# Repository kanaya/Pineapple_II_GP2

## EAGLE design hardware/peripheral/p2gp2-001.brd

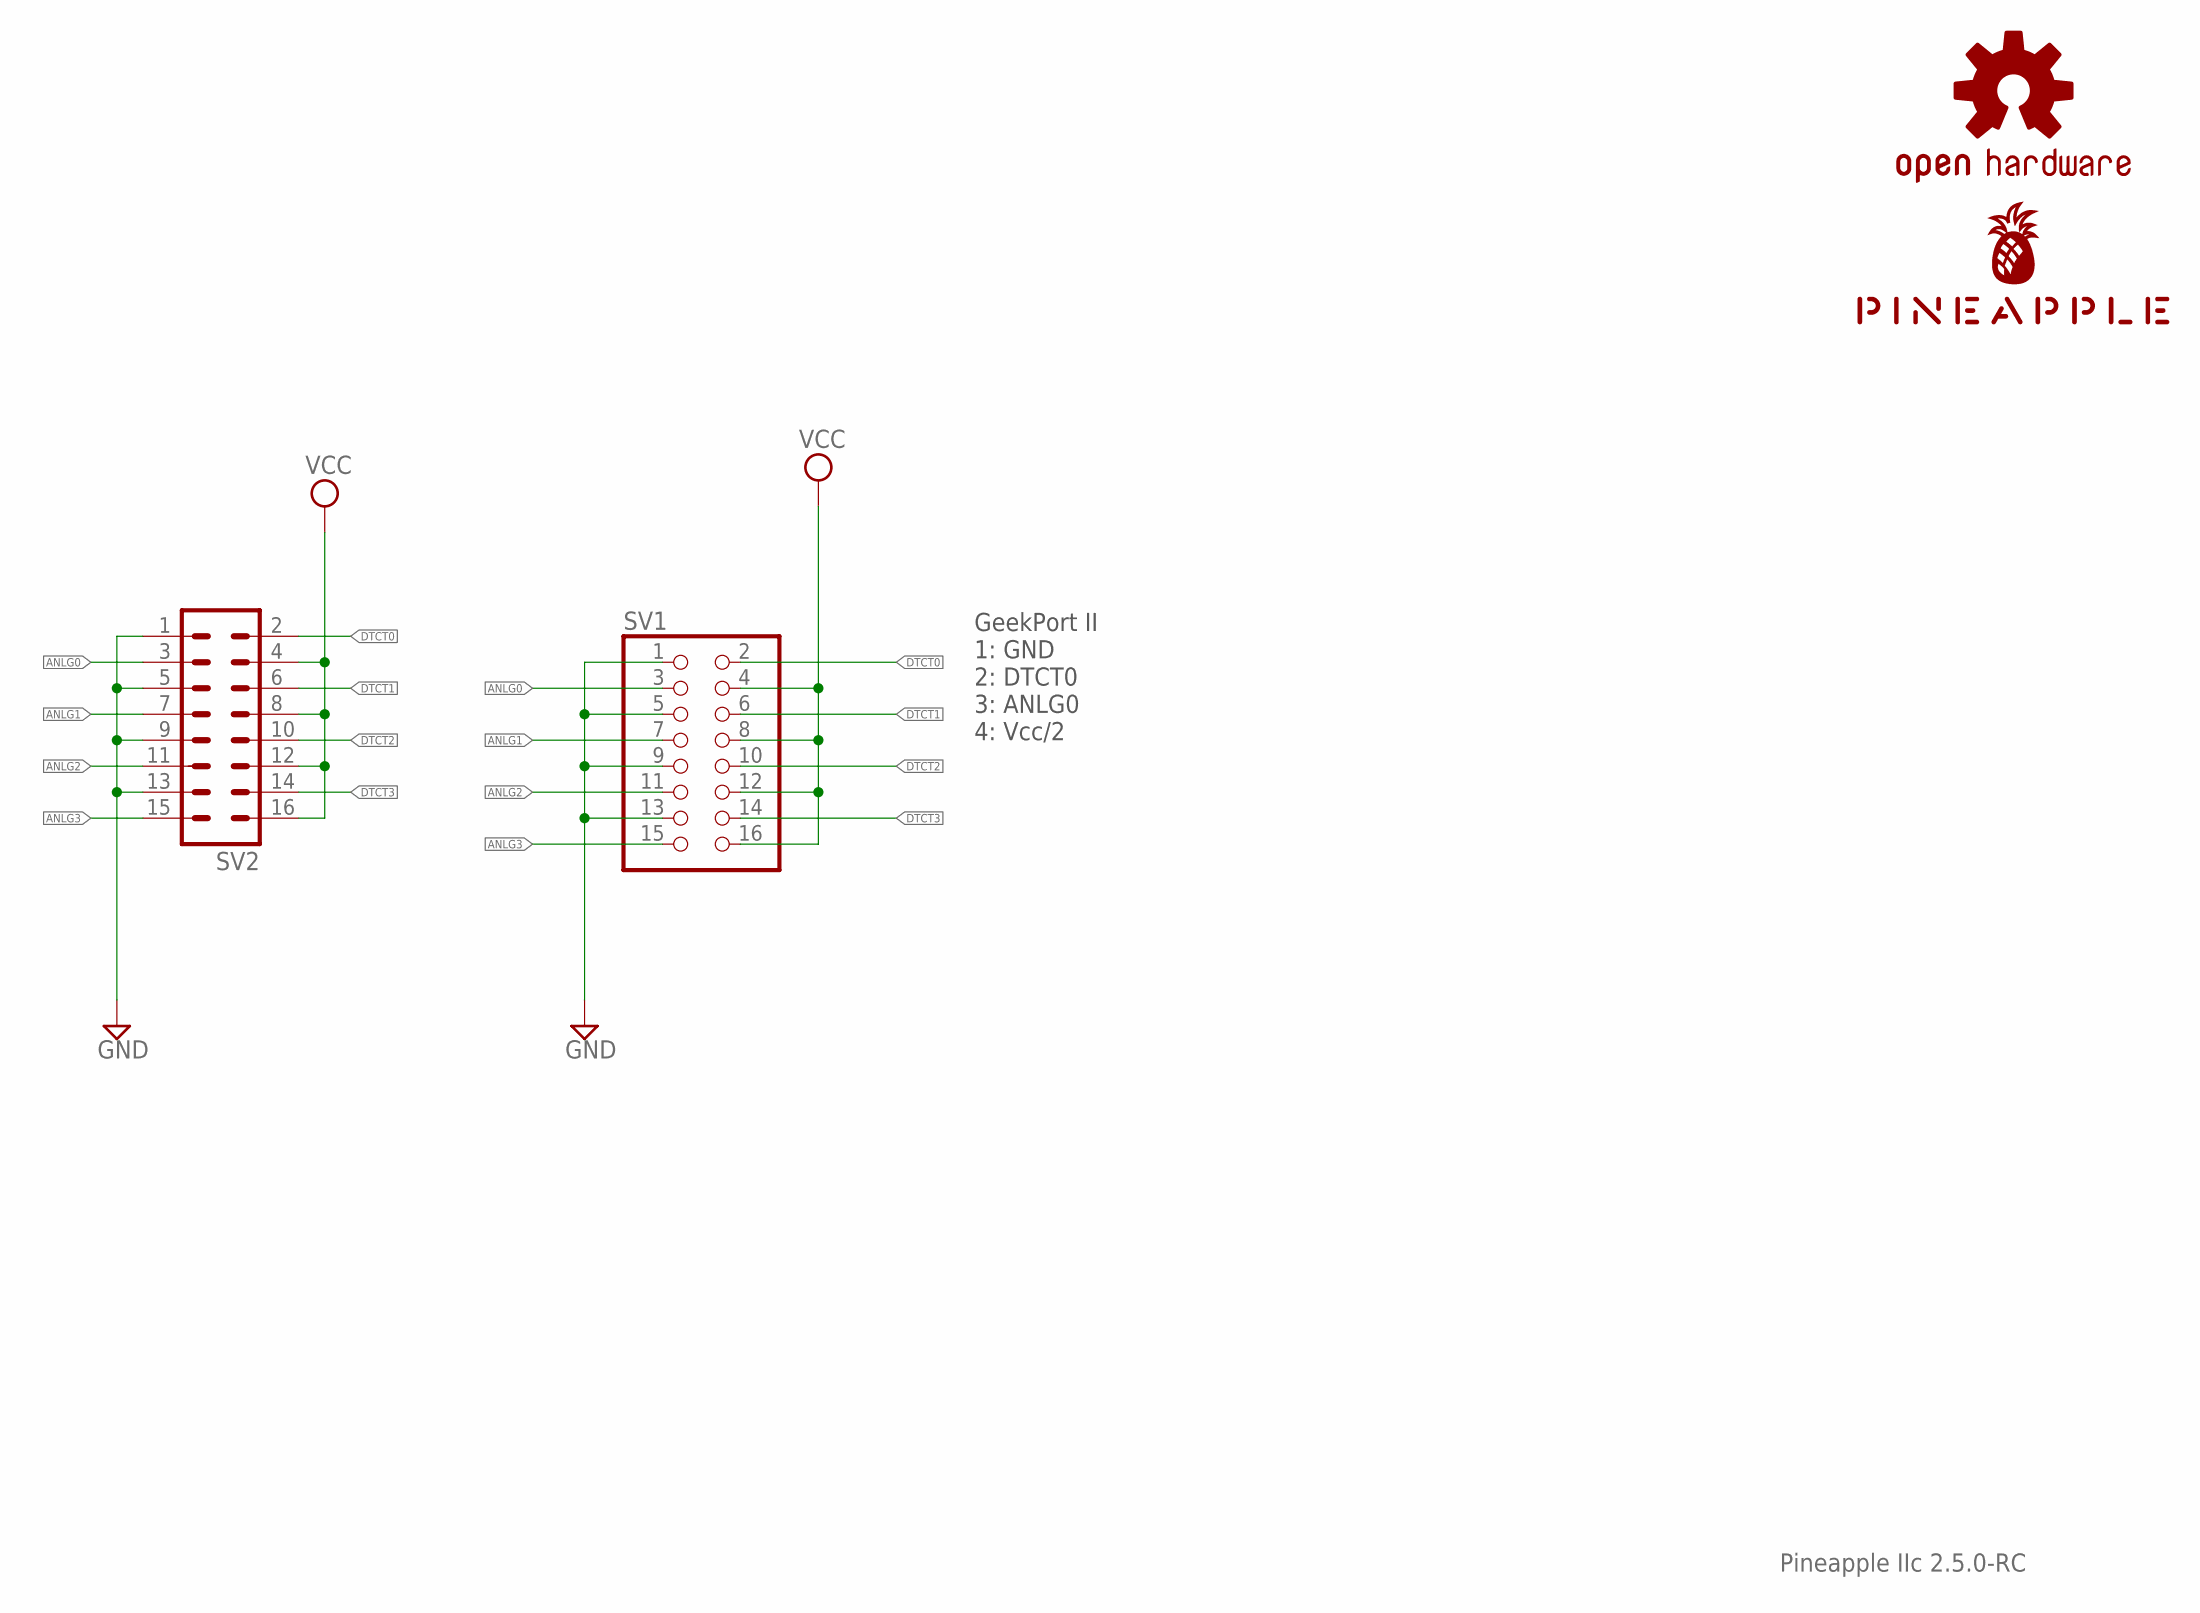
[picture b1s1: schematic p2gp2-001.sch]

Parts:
LOGO1: OSHW-LOGOS-COPPER; OSHW-LOGO-S_COPPER
SV1: PINHD-2X8; 2X08
SV2: ML16
U$1: PINEAPPLE450_SILK

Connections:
ANLG0: SV1.3, SV2.3
ANLG1: SV1.7, SV2.7
ANLG2: SV1.11, SV2.11
ANLG3: SV1.15, SV2.15
DTCT0: SV1.2, SV2.2
DTCT1: SV1.6, SV2.6
DTCT2: SV1.10, SV2.10
DTCT3: SV1.14, SV2.14
GND: SV1.1, SV1.5, SV1.9, SV1.13, SV2.1, SV2.5, SV2.9, SV2.13
VCC: SV1.4, SV1.8, SV1.12, SV1.16, SV2.4, SV2.8, SV2.12, SV2.16

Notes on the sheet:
Pineapple IIc 2.5.0-RC
GeekPort II 1: GND 2: DTCT0 3: ANLG0 4: Vcc/2

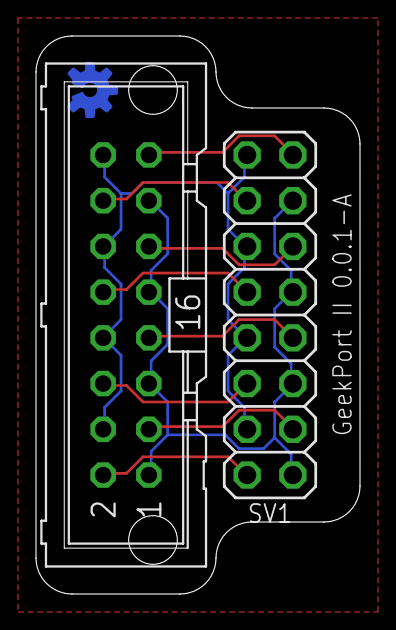
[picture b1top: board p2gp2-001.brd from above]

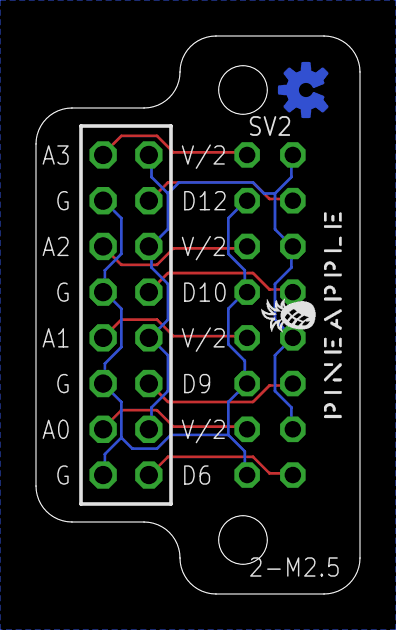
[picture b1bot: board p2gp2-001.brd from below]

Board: 2 copper layers, 18.0 x 31.0 mm, 4 parts (2 on the bottom side), 10 nets.

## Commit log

2022-09-18 Initial commit. (Imported from HEX SW.)
2022-09-18 Clean up.
2022-09-18 First working model.

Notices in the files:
parts and their libraries:
SparkFun-Aesthetics: Licensing: Creative Commons ShareAlike 4.0 International - https://creativecommons.org/licenses/by-sa/4.0
